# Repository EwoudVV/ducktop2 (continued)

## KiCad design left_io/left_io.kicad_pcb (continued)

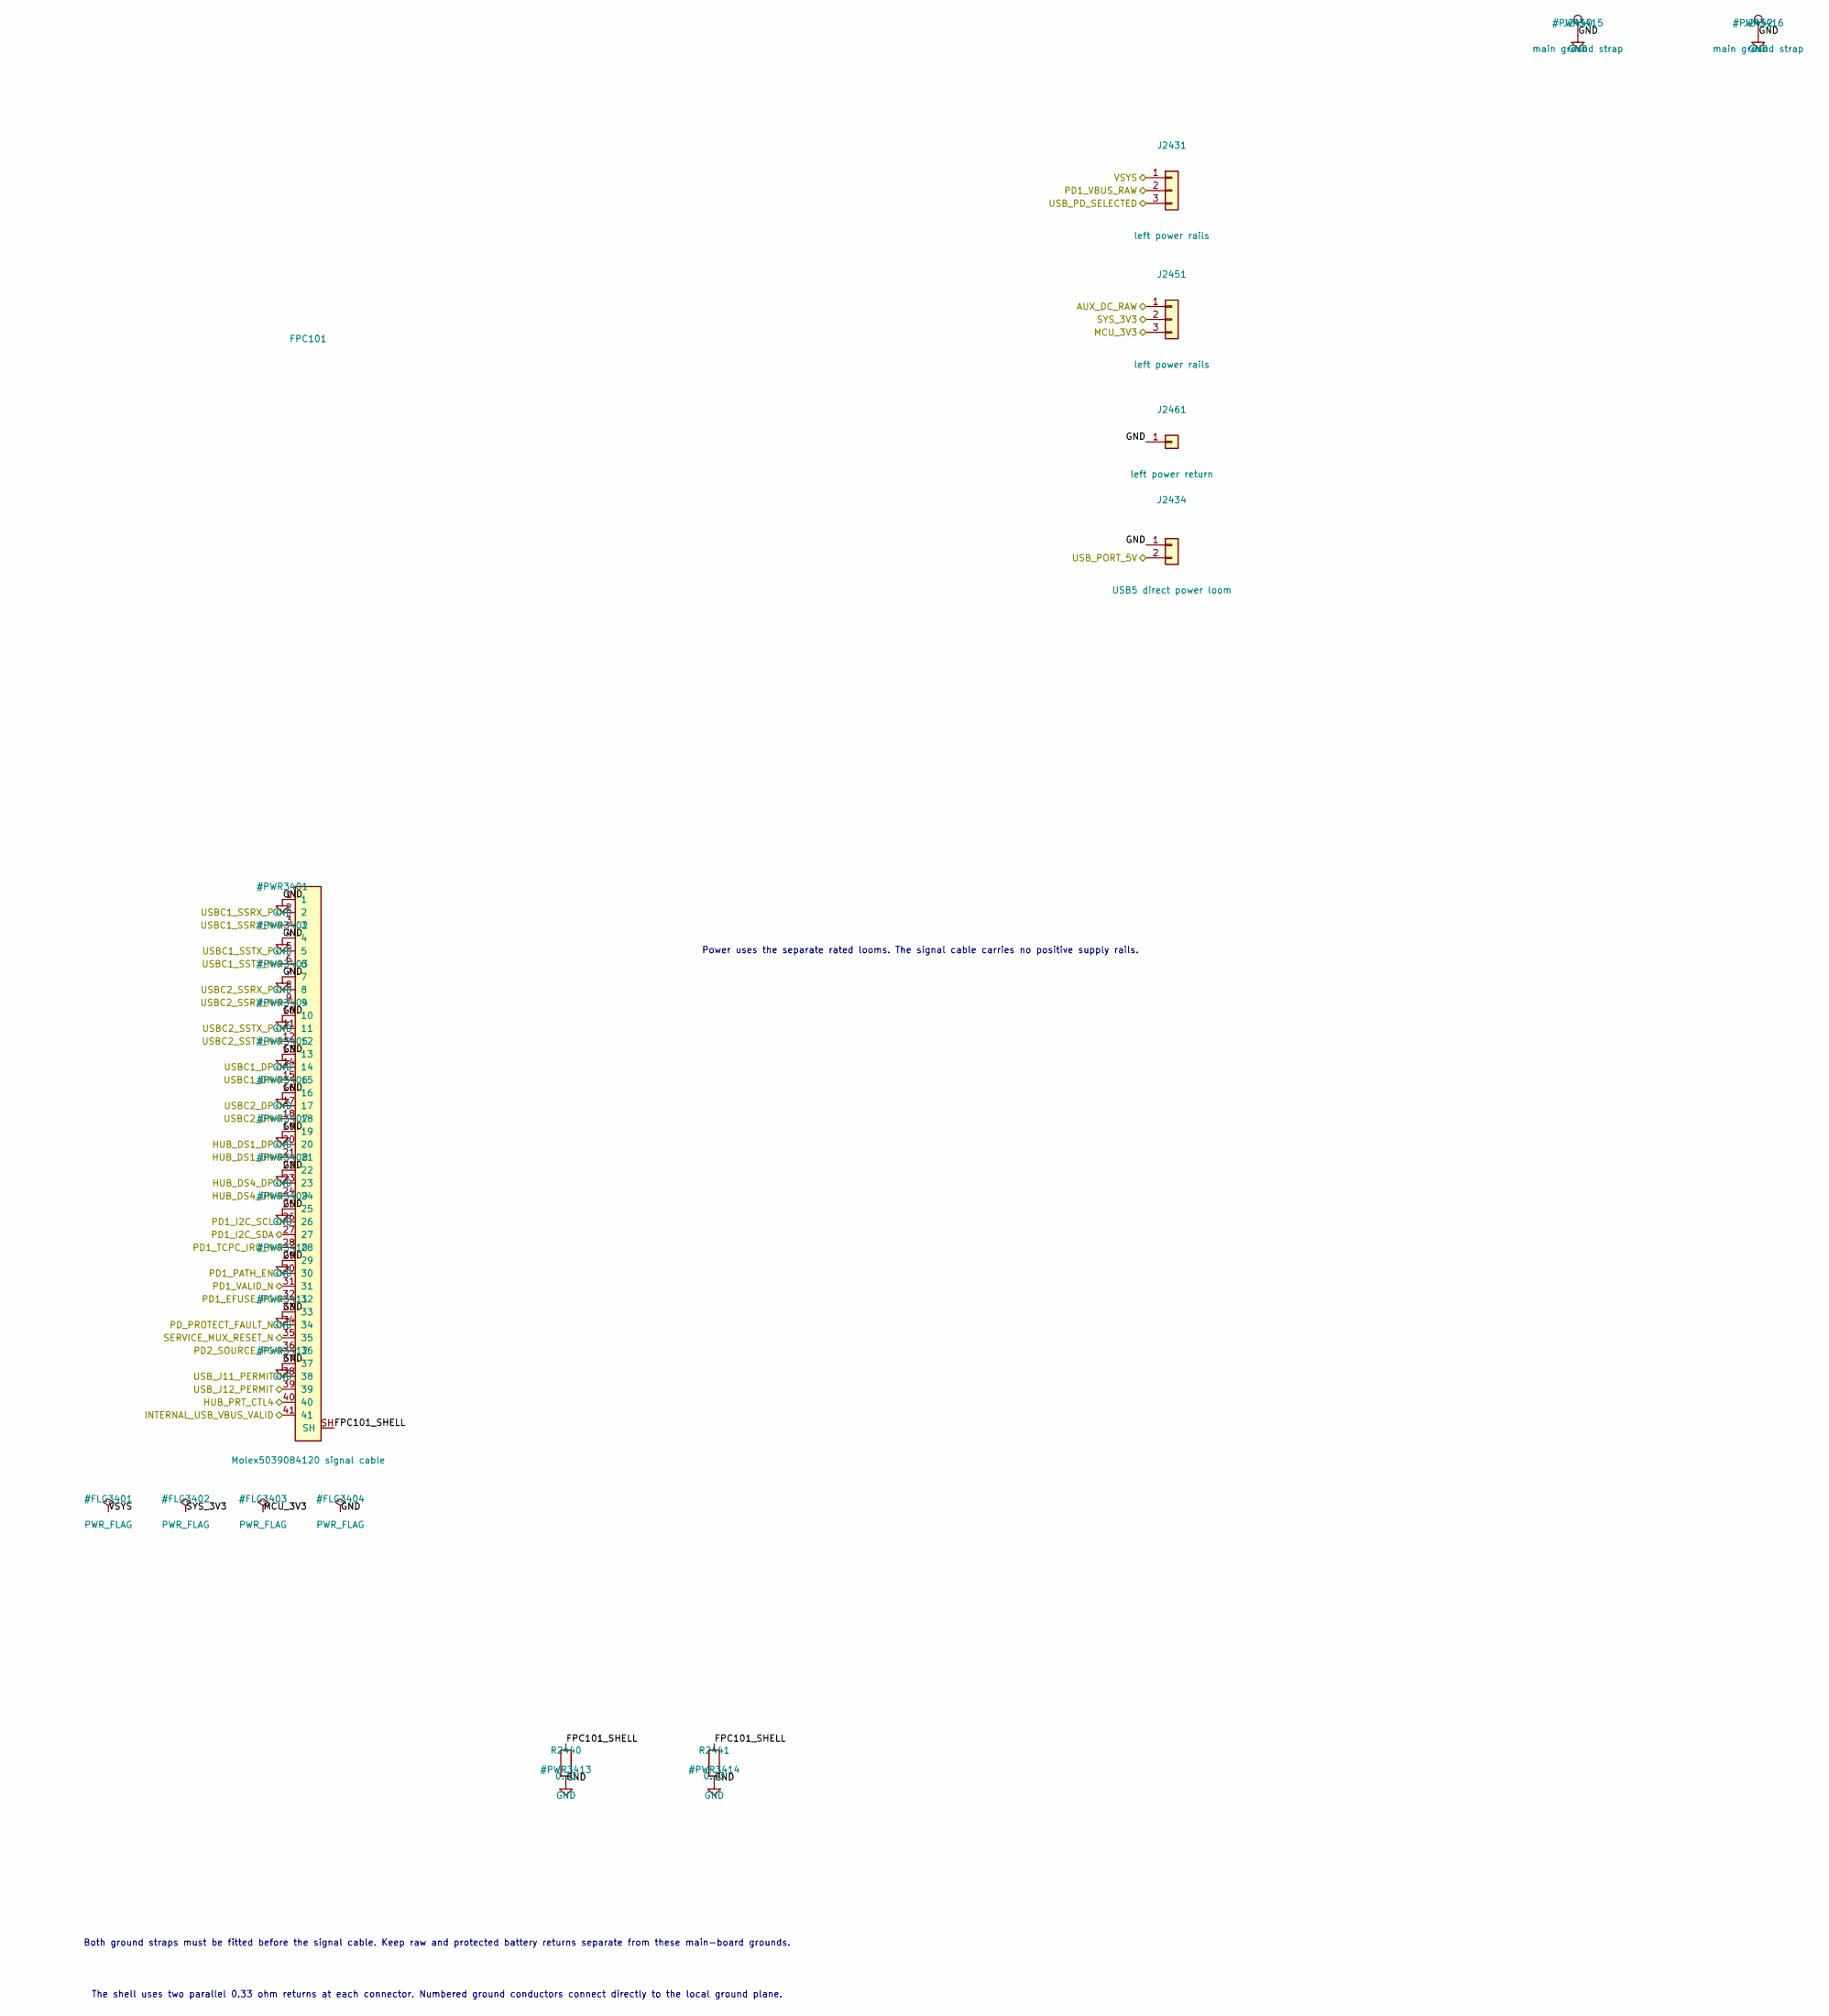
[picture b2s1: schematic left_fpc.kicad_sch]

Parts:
FPC101: Molex5039084120 signal cable; Molex_5039084120_1x41_P0.50mm_Horizontal; MPN 5039084120
J2431, J2451: left power rails; WAGO_2060_453_SMD; MPN 2060-453/998-404
J2434: USB5 direct power loom; AMASS_XT30PW-F30_G_Y; MPN XT30PW-F30.G.Y
J2440, J2442: main ground strap; SolderWirePad_1x01_SMD_5x10mm
J2461: left power return; WAGO_2060_451_SMD; MPN 2060-451/998-404
R2440, R2441: 0.33; R_0603_1608Metric; MPN ERJ3RQFR33V

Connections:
/AUX_DC_RAW: J2451.1; also elsewhere on the board
/FPC-1 (to Center)/FPC101_SHELL: FPC101.SH, R2440.1, R2441.1
/HUB_DS1_DN: FPC101.21; also elsewhere on the board
/HUB_DS1_DP: FPC101.20; also elsewhere on the board
/HUB_DS4_DN: FPC101.24; also elsewhere on the board
/HUB_DS4_DP: FPC101.23; also elsewhere on the board
/HUB_PRT_CTL4: FPC101.40; also elsewhere on the board
/INTERNAL_USB_VBUS_VALID: FPC101.41; also elsewhere on the board
/MCU_3V3: J2451.3; also elsewhere on the board
/PD1_EFUSE_PG: FPC101.32; also elsewhere on the board
/PD1_I2C_SCL: FPC101.26; also elsewhere on the board
/PD1_I2C_SDA: FPC101.27; also elsewhere on the board
/PD1_PATH_EN: FPC101.30; also elsewhere on the board
/PD1_TCPC_IRQ_N: FPC101.28; also elsewhere on the board
/PD1_VALID_N: FPC101.31; also elsewhere on the board
/PD1_VBUS_RAW: J2431.2; also elsewhere on the board
/PD2_SOURCE_PG: FPC101.36; also elsewhere on the board
/PD_PROTECT_FAULT_N: FPC101.34; also elsewhere on the board
/SERVICE_MUX_RESET_N: FPC101.35; also elsewhere on the board
/SYS_3V3: J2451.2; also elsewhere on the board
/USBC1_DN: FPC101.15; also elsewhere on the board
/USBC1_DP: FPC101.14; also elsewhere on the board
/USBC1_SSRX_N: FPC101.3; also elsewhere on the board
/USBC1_SSRX_P: FPC101.2; also elsewhere on the board
/USBC1_SSTX_N: FPC101.6; also elsewhere on the board
/USBC1_SSTX_P: FPC101.5; also elsewhere on the board
/USBC2_DN: FPC101.18; also elsewhere on the board
/USBC2_DP: FPC101.17; also elsewhere on the board
/USBC2_SSRX_N: FPC101.9; also elsewhere on the board
/USBC2_SSRX_P: FPC101.8; also elsewhere on the board
/USBC2_SSTX_N: FPC101.12; also elsewhere on the board
/USBC2_SSTX_P: FPC101.11; also elsewhere on the board
/USB_J11_PERMIT: FPC101.38; also elsewhere on the board
/USB_J12_PERMIT: FPC101.39; also elsewhere on the board
/USB_PD_SELECTED: J2431.3; also elsewhere on the board
/USB_PORT_5V: J2434.2; also elsewhere on the board
/VSYS: J2431.1; also elsewhere on the board
GND: FPC101.1, FPC101.4, FPC101.7, FPC101.10, FPC101.13, FPC101.16, FPC101.19, FPC101.22, FPC101.25, FPC101.29, FPC101.33, FPC101.37, J2434.1, J2440.1, J2442.1, J2461.1, R2440.2, R2441.2; also elsewhere on the board

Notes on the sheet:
Power uses the separate rated looms. The signal cable carries no positive supply rails.
Both ground straps must be fitted before the signal cable. Keep raw and protected battery returns separate from these main-board grounds.
The shell uses two parallel 0.33 ohm returns at each connector. Numbered ground conductors connect directly to the local ground plane.

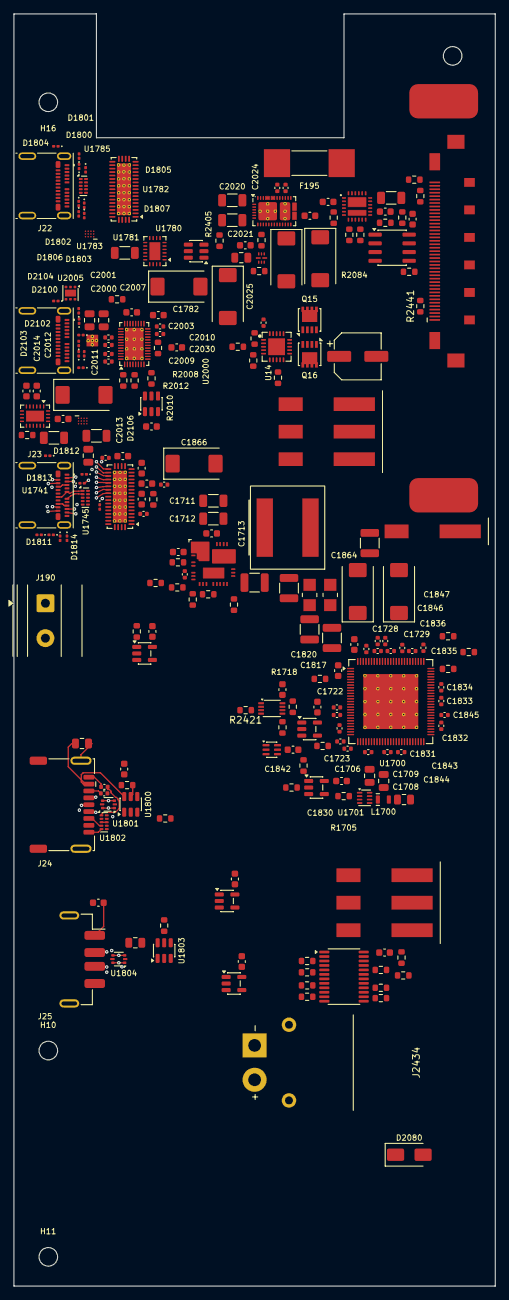
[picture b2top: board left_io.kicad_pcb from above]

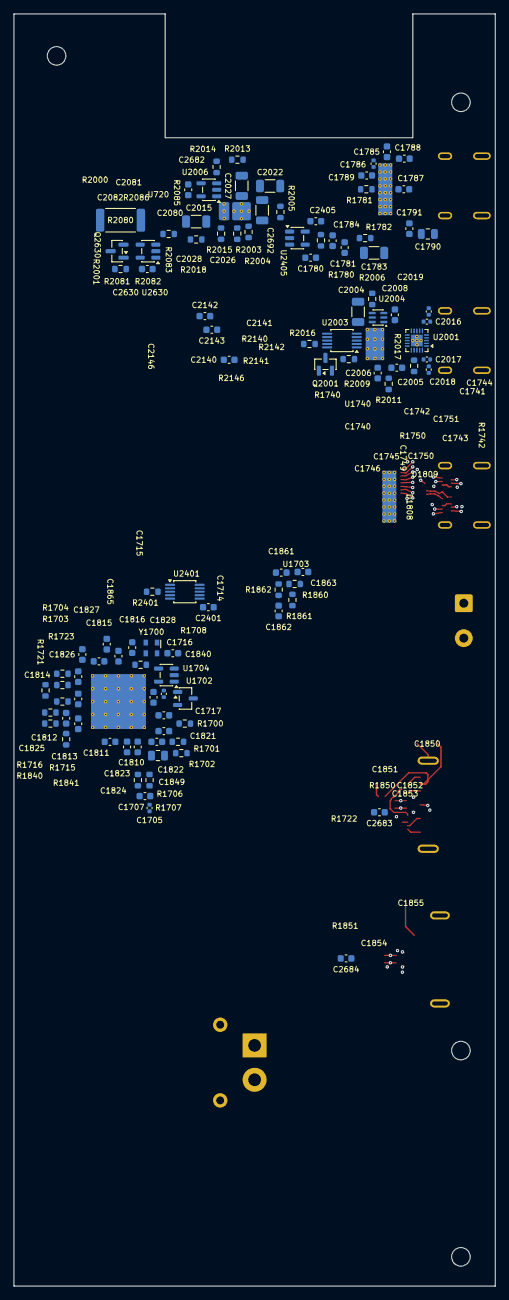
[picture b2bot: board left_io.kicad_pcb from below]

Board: 8 copper layers, 70.0 x 185.0 mm, 334 parts (103 on the bottom side), 220 nets.

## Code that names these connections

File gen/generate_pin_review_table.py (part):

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

def add_lm706a0(ref: str, prefix: str, sense: str, output: str, power_good: str) -> None:
    add_many(ref, (1, 2, 3, 27, 28, 29), "/VSYS", "All six converter input pins use VSYS.", LM706_SOURCE)
    add_many(ref, (6, 8, 17, 23, 24, 25, 26, 30), "GND",
             "Internal bias, forced PWM, analog ground and power/thermal returns.", LM706_SOURCE)
    for pin, suffix in {4: "BOOT", 5: "SW_BOOT", 9: "EN", 13: "CONFIG", 14: "RT",
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    clear_ref_contracts("U2", "U5", "U750", "U718", "U2660")
    add("U64", 3, "/Internal Services/TRACKPAD_EN", "Trackpad supply follows its hardware-qualified enable.", "gen/verify_design_contracts.py")
    aliases = {"/EC & MCU/NRST_NET":"/NRST_NET", "/PMIC_QON_ASSERT":"/MU_PROCHOT_RELEASE",
               "/PD1_EFUSE_FAULT_N":"/PD1_EFUSE_PG", "/PD2_EFUSE_FAULT_N":"/PD2_EFUSE_PG"}
    for key, contract in list(contracts.items()):
        if contract.expected in aliases:
            contracts[key] = Contract(aliases[contract.expected], "Reset and source-control signal for the 100 W power revision.",
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
    # Battery power entry and aux/random DC input.
    for pin in (1, 2):
        add("J2", pin, "/Power & Battery/PACK_POS_RAW", "Paired raw pack-positive power contact.", "Ducktop2 autonomous 3S protection contract")
    for pin in (3, 4):
        add("J2", pin, "/Power & Battery/PACK_NEG_RAW", "Paired raw pack-negative power contact before protector shunt/FETs.", "Ducktop2 autonomous 3S protection contract")
    add("J2", 5, "/Power & Battery/CELL1_TAP", "Cell-1 positive / cell-2 negative balance tap.", "TI BQ77915 3S connection contract")
    add("J2", 6, "/Power & Battery/CELL2_TAP", "Cell-2 positive / cell-3 negative balance tap.", "TI BQ77915 3S connection contract")
    add("F1", 1, "/Power & Battery/PACK_POS_RAW", "Main pack fuse input is raw pack positive.", "Ducktop2 battery safety review")
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    ):
        add(ref, pin, net, note, "Analog Devices LTC4368-1 latch/retry contract")
    for ref, drain in [("Q11", "/Power & Battery/BAT_PROT_VIN"), ("Q12", "/Power & Battery/BAT_PROT_SENSE")]:
        add_many(ref, [1, 2, 3], "/Power & Battery/BAT_PROT_FET_COMMON", "Back-to-back MOSFET source pins share the protected common-source node.", "Analog Devices LTC4368-1 reverse-protection topology")
        add(ref, 4, "/Power & Battery/BAT_PROT_GATE", "MOSFET gate is driven through the protected gate network.", "Analog Devices LTC4368-1 reverse-protection topology")
        add(ref, 5, drain, "MOSFET drain terminates its side of the protected pack path.", "Analog Devices LTC4368-1 reverse-protection topology")
    add("RS10", 1, "/Power & Battery/BAT_PROT_SENSE", "High-side shunt controller-side sense node.", "Ducktop2 protected-pack contract")
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                16:"SEL_STAGE2", 17:"/USB_PD_SELECTED", 18:"MAIN_SEL_INTVCC",
                19:"MAIN_SEL_INTVCC", 20:"GND", 21:"GND"},
        "U16": {1:"ST2_SEL_TMR", 2:"ST2_USB_UV", 3:"ST2_USB_OV",
                 4:"ST2_AUX_UV", 5:"ST2_AUX_OV", 6:"/PD2_VALID_N", 8:"GND",
                 10:"ST2_SEL_INTVCC", 11:"ST2_AUX_GATE", 12:"ST2_AUX_FET_COMMON",
                 13:"ST2_USB_GATE", 14:"ST2_USB_FET_COMMON", 15:"SEL_STAGE2",
                 16:"AUX_DC_PROTECTED", 17:"/PD2_VBUS_GATED", 18:"ST2_SEL_INTVCC",
                 19:"ST2_SEL_INTVCC", 20:"GND", 21:"GND"},
    }
    def selector_net(name):
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        ("Q22", "USB_MAIN_GATE", "USB_MAIN_FET_COMMON", "VBUS_COMBINED"),
        ("Q23", "ST2_AUX_GATE", "ST2_AUX_FET_COMMON", "AUX_DC_PROTECTED"),
        ("Q24", "ST2_AUX_GATE", "ST2_AUX_FET_COMMON", "SEL_STAGE2"),
        ("Q26", "ST2_USB_GATE", "ST2_USB_FET_COMMON", "/PD2_VBUS_GATED"),
        ("Q27", "ST2_USB_GATE", "ST2_USB_FET_COMMON", "SEL_STAGE2"),
        ("Q28", "ST2_MAIN_GATE", "ST2_MAIN_FET_COMMON", "SEL_STAGE2"),
        ("Q29", "ST2_MAIN_GATE", "ST2_MAIN_FET_COMMON", "VBUS_COMBINED"),
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        ("R730", "/USB_PD_SELECTED", "USB_MAIN_UV"), ("R731", "USB_MAIN_UV", "USB_MAIN_OV"),
        ("R732", "USB_MAIN_OV", "GND"), ("R733", "AUX_DC_PROTECTED", "ST2_AUX_UV"),
        ("R734", "ST2_AUX_UV", "ST2_AUX_OV"), ("R735", "ST2_AUX_OV", "GND"),
        ("R741", "/PD2_VBUS_GATED", "ST2_USB_UV"), ("R742", "ST2_USB_UV", "ST2_USB_OV"),
        ("R743", "ST2_USB_OV", "GND"), ("R744", "SEL_STAGE2", "ST2_MAIN_UV"),
        ("R745", "ST2_MAIN_UV", "ST2_MAIN_OV"), ("R746", "ST2_MAIN_OV", "GND"),
    ):
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        ("C747", "ST2_MAIN_FET_COMMON"), ("C748", "SEL_STAGE2"),
        ("C749", "ST2_SEL_INTVCC"), ("C715", "ST2_SEL_TMR"),
        ("C746", "VBUS_COMBINED"), ("C2685", "SEL_STAGE2"),
        ("C2686", "/PD2_VBUS_GATED"), ("C2687", "ST2_USB_FET_COMMON"),
        ("C2688", "VBUS_COMBINED"),
    ):
        add(ref, 1, selector_net(net), "Selector bypass, hold-up, or timer capacitor.", selector)
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    for ref, source in (
        ("D710", "/Power & Battery/BAT_CHARGER"),
        ("D711", "/Power & Battery/AUX_DC_PROTECTED"),
        ("D712", "/PD1_VBUS_RAW"),
        ("D713", "/PD2_VBUS_RAW"),
        ("D714", "/PD3_VBUS_RAW"),
    ):
        add(ref, 1, "/Power & Battery/AON_OR_RAW", "Schottky cathode joins the aggregate always-on eFuse input.", aon_or)
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        9: "/Power & Battery/VBUS_COMBINED",
        10: "GND",
        11: "GND",
        12: "/Power & Battery/PMIC_QON_PIN",
        13: "/Power & Battery/CHG_CE_HW_N",
        14: "/I2C_SCL",
        15: "/I2C_SDA",
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    add("R705", 1, "/Power & Battery/CHG_TS_FIXED", "Fixed TS divider bottom holds a valid room-temperature ratio.", bq)
    add("R705", 2, "GND", "Fixed TS divider returns to ground.", bq)
    for pin in (1, 2, 3):
        add("Q25", pin, "/Power & Battery/BAT_CHARGER", "BQ25798 ship-FET source is on the charger-side BAT node.", bq)
    add("Q25", 4, "/Power & Battery/SDRV_GATE", "BQ25798 SDRV directly controls the qualified ship FET gate.", bq)
    add("Q25", 5, "/PACK_POS_FUSED", "Ship-FET drain connects to the protected pack for electronic ship/hard-off.", bq)
    for ref, pin, net, note in (
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        ("R13", 2, "GND", "QON gate pull-down return."),
        ("Q702", 1, "/PMIC_QON_ASSERT", "Active-high EC pulse drives the QON open-drain gate."),
        ("Q702", 2, "GND", "QON open-drain source."),
        ("Q702", 3, "/Power & Battery/PMIC_QON_PIN", "QON open-drain drain; no dead-rail pull-up is allowed."),
        ("D715", 1, "/CASE_PWRBTN_N", "Case-button cathode shared only by the two isolation diodes."),
        ("D715", 2, "/Power & Battery/PMIC_QON_PIN", "Case button can wake the BQ25798 through a Schottky anode."),
        ("D716", 1, "/CASE_PWRBTN_N", "Case-button cathode shared only by the two isolation diodes."),
        ("D716", 2, "/MU_PWRBTN_N", "Case button reaches Mu PWRBTN through an independent Schottky anode."),
    ):
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
    # EC buck and core STM32 pins that are easy to get catastrophically wrong.
    stm = "ST STM32F407 datasheet plus Ducktop2 EC core contract"
    add_many("U4", [6, 11, 19, 21, 22, 28, 50, 75, 100], "/MCU_3V3", "STM32 VDD/VBAT/VDDA pins require 3.3 V rail.", stm)
    add_many("U4", [10, 20, 27, 74, 99], "GND", "STM32 VSS/VSSA pins require ground.", stm)
    for pin, net in {49: "/EC & MCU/VCAP1_NODE", 73: "/EC & MCU/VCAP2_NODE", 94: "/EC & MCU/BOOT0_NET", 14: "/EC & MCU/NRST_NET", 72: "/EC & MCU/SWDIO_NET", 76: "/EC & MCU/SWCLK_NET"}.items():
        add("U4", pin, net, "STM32 reset, boot, SWD, and VCAP pins follow the EC core contract.", stm)
    for pin, net in {8: "/EC & MCU/LSE_IN", 9: "/EC & MCU/LSE_OUT",
                     12: "/EC & MCU/HSE_IN", 13: "/EC & MCU/HSE_OUT"}.items():
        add("U4", pin, net, "STM32 oscillator pin follows the qualified prototype oscillator contract.", stm)
    for pin, net, requirement in [
        (47, "/RADIO_VHF_UART_TX", "PB10 is USART3_TX for VHF radio hardware UART."),
        (48, "/RADIO_VHF_UART_RX", "PB11 is USART3_RX for VHF radio hardware UART."),
        (63, "/RADIO_UHF_UART_TX", "PC6 is USART6_TX for UHF radio hardware UART."),
        (64, "/RADIO_UHF_UART_RX", "PC7 is USART6_RX for UHF radio hardware UART."),
        (67, "/WIFI_W_DISABLE1_N_EC", "PA8 drives the powered-off-isolated WLAN disable input."),
        (68, "/GNSS_UART_TX", "PA9 is USART1_TX for GNSS hardware UART."),
        (69, "/GNSS_UART_RX", "PA10 is USART1_RX for GNSS hardware UART."),
        (77, "/WIFI_W_DISABLE2_N_EC", "PA15 drives the powered-off-isolated Bluetooth disable input."),
        (36, "/TRACKPAD_FAULT_N", "PB1 reads the trackpad current-limited branch fault output."),
        (44, "/MU_12V_ENABLE", "PE13 explicitly enables the regulated Mu 12 V rail after source qualification."),
        (45, "/MU_S0_HIGH", "PE14 reads the Mu PSON/S0 status signal."),
        (46, "/MU_12V_PG", "PE15 reads the regulated Mu 12 V power-good signal."),
        (42, "/AUDIO_MIC_EN", "PE11 controls the fail-off microphone rail; the privacy indicator monitors the actual MIC_2V8 output."),
        (15, "/KB_RGB_PWR_EN", "PC0 enables both the current-limited keyboard RGB rail and its level buffer."),
        (16, "/KB_RGB_FAULT_N", "PC1 reads the active-low keyboard RGB power-switch fault output."),
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
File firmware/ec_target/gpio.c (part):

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    GPIOC->ODR = (1u << 8) | (1u << 9) | (1u << 10);
    GPIOD->ODR = 0u;
    GPIOE->ODR = 0u;
    /* Preserve SWD on PA13/PA14 through normal startup. */
    GPIOA->MODER = (2u << 26) | (2u << 28);
    GPIOA->PUPDR = (1u << 26) | (2u << 28);
    GPIOA->AFR[1] &= ~((0xFu << 20) | (0xFu << 24));
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
    /* ---- Port A ---- */

    /* PA0: MU_PWRBTN_N - Output, open-drain, high (inactive) */
    GPIOA->MODER   |= GPIO_MODER_OUTPUT << (0 * 2);
    GPIOA->OTYPER  |= GPIO_OTYPER_OD << 0;
    GPIOA->PUPDR   |= GPIO_PUPDR_PU << (0 * 2);
    GPIOA->ODR     |= 1u << 0;

    /* PA1: BQ_ALERT - Input, pull-up */
    GPIOA->PUPDR   |= GPIO_PUPDR_PU << (1 * 2);

    /* PA2: CHG_INT_N - Input, pull-up */
    GPIOA->PUPDR   |= GPIO_PUPDR_PU << (2 * 2);

    /* PA3: MU_PROCHOT_RELEASE - low keeps the module throttled. */
    GPIOA->MODER   |= GPIO_MODER_OUTPUT << (3 * 2);

    /* PA4: CHG_ENABLE - Output, push-pull, low (charger off) */
    GPIOA->MODER   |= GPIO_MODER_OUTPUT << (4 * 2);

    /* PA5: MU_RSTBTN_N - Output, open-drain, high (inactive) */
    GPIOA->MODER   |= GPIO_MODER_OUTPUT << (5 * 2);
    GPIOA->OTYPER  |= GPIO_OTYPER_OD << 5;
    GPIOA->ODR     |= 1u << 5;

    /* PA6: AUX_DC_ADC - Analog */
    GPIOA->MODER   |= GPIO_MODER_ANALOG << (6 * 2);

    /* PA7: THERM_SKIN_ADC - Analog */
    GPIOA->MODER   |= GPIO_MODER_ANALOG << (7 * 2);

    /* PA8: WIFI_W_DISABLE1_N_EC - Output, push-pull, high (disabled) */
    GPIOA->MODER   |= GPIO_MODER_OUTPUT << (8 * 2);
    GPIOA->ODR     |= 1u << 8;

    /* PA9: GNSS_UART_TX - AF7 (USART1) */
    GPIOA->MODER   |= GPIO_MODER_AF << (9 * 2);
    GPIOA->AFR[1]     = (GPIOA->AFR[1] & ~(0xFu << 4)) | (GPIO_AF7 << 4);

    /* PA10: GNSS_UART_RX - AF7 (USART1) */
    GPIOA->MODER   |= GPIO_MODER_AF << (10 * 2);
    GPIOA->AFR[1]     = (GPIOA->AFR[1] & ~(0xFu << 8)) | (GPIO_AF7 << 8);

    /* PA11: MCU_USB_DN - AF10 (OTG_FS) */
    GPIOA->MODER   |= GPIO_MODER_AF << (11 * 2);
    GPIOA->AFR[1]     = (GPIOA->AFR[1] & ~(0xFu << 12)) | (GPIO_AF10 << 12);

    /* PA12: MCU_USB_DP - AF10 (OTG_FS) */
    GPIOA->MODER   |= GPIO_MODER_AF << (12 * 2);
    GPIOA->AFR[1]     = (GPIOA->AFR[1] & ~(0xFu << 16)) | (GPIO_AF10 << 16);

    /* PA13: SWDIO - leave as default (AF0, pull-up) */

    /* PA14: SWCLK - leave as default (AF0, pull-down) */

    /* PA15: WIFI_W_DISABLE2_N_EC - Output, push-pull, high (disabled) */
    GPIOA->MODER   |= GPIO_MODER_OUTPUT << (15 * 2);
    GPIOA->ODR     |= 1u << 15;

    /* ---- Port B ---- */

    /* PB0: THERM_MU_ADC - Analog */
    GPIOB->MODER   |= GPIO_MODER_ANALOG << (0 * 2);

    /* PB1: TRACKPAD_FAULT_N - Input, pull-up */
    GPIOB->PUPDR   |= GPIO_PUPDR_PU << (1 * 2);

    /* PB2: PD2_VALID_N - Input, pull-up */
    GPIOB->PUPDR   |= GPIO_PUPDR_PU << (2 * 2);

    /* PB3: (JTDO/SWO) - leave as default */

    /* PB4: PD2_TCPC_IRQ_N - Input, pull-up */
    GPIOB->PUPDR   |= GPIO_PUPDR_PU << (4 * 2);

    /* PB5: RADIO_DB_PWR_EN - Output, push-pull, low (off) */
    GPIOB->MODER   |= GPIO_MODER_OUTPUT << (5 * 2);

    /* PB6: I2C1_SCL - AF4 */
    GPIOB->MODER   |= GPIO_MODER_AF << (6 * 2);
    GPIOB->OTYPER  |= GPIO_OTYPER_OD << 6;
    GPIOB->PUPDR   |= GPIO_PUPDR_PU << (6 * 2);
    GPIOB->OSPEEDR |= GPIO_OSPEEDR_HIGH << (6 * 2);
    GPIOB->AFR[0]     = (GPIOB->AFR[0] & ~(0xFu << 24)) | (GPIO_AF4 << 24);

    /* PB7: I2C1_SDA - AF4 */
    GPIOB->MODER   |= GPIO_MODER_AF << (7 * 2);
    GPIOB->OTYPER  |= GPIO_OTYPER_OD << 7;
    GPIOB->PUPDR   |= GPIO_PUPDR_PU << (7 * 2);
    GPIOB->OSPEEDR |= GPIO_OSPEEDR_HIGH << (7 * 2);
    GPIOB->AFR[0]     = (GPIOB->AFR[0] & ~(0xFu << 28)) | (GPIO_AF4 << 28);

    /* PB8: GNSS_EXTINT - Input, pull-down */
    GPIOB->PUPDR   |= GPIO_PUPDR_PD << (8 * 2);

    /* PB9: PD_PROTECT_FAULT_N - Input, pull-up */
    GPIOB->PUPDR   |= GPIO_PUPDR_PU << (9 * 2);

    /* PB10: RADIO_VHF_UART_TX - AF7 (USART3) */
    GPIOB->MODER   |= GPIO_MODER_AF << (10 * 2);
    GPIOB->AFR[1]     = (GPIOB->AFR[1] & ~(0xFu << 8)) | (GPIO_AF7 << 8);

    /* PB11: RADIO_VHF_UART_RX - AF7 (USART3) */
    GPIOB->MODER   |= GPIO_MODER_AF << (11 * 2);
    GPIOB->AFR[1]     = (GPIOB->AFR[1] & ~(0xFu << 12)) | (GPIO_AF7 << 12);

    /* PB12: SERVICE_MUX_RESET_REQ_N - Output, push-pull, low (reset held) */
    GPIOB->MODER   |= GPIO_MODER_OUTPUT << (12 * 2);

    /* PB13: GNSS_RESET_N - Output, push-pull, low (reset asserted) */
    GPIOB->MODER   |= GPIO_MODER_OUTPUT << (13 * 2);

    /* PB14: GNSS_PPS - Input, pull-down */
    GPIOB->PUPDR   |= GPIO_PUPDR_PD << (14 * 2);

    /* PB15: RADIO_VHF_PTT_N - Output, push-pull, high (inactive) */
    GPIOB->MODER   |= GPIO_MODER_OUTPUT << (15 * 2);
    GPIOB->ODR     |= 1u << 15;

    /* ---- Port C ---- */

    /* PC0: KB_RGB_PWR_EN - Output, push-pull, low (off) */
    GPIOC->MODER   |= GPIO_MODER_OUTPUT << (0 * 2);

    /* PC1: KB_RGB_FAULT_N - Input, pull-up */
    GPIOC->PUPDR   |= GPIO_PUPDR_PU << (1 * 2);

    /* PC2: RADIO_VHF_RF_SEL_3V3 - Output, push-pull, low */
    GPIOC->MODER   |= GPIO_MODER_OUTPUT << (2 * 2);

    /* PC3: RADIO_UHF_RF_SEL_3V3 - Output, push-pull, low */
    GPIOC->MODER   |= GPIO_MODER_OUTPUT << (3 * 2);

    /* PC4: PD1_VALID_N - Input, pull-up */
    GPIOC->PUPDR   |= GPIO_PUPDR_PU << (4 * 2);

    /* PC5: FAN_TACH - Input, no internal pull (R206 8.2k to MCU_3V3 idles
     * the open-collector FG line high; C209 3.9n filters it) */
    GPIOC->MODER   |= GPIO_MODER_INPUT << (5 * 2);

    /* PC6: RADIO_UHF_UART_TX - AF8 (USART6) */
    GPIOC->MODER   |= GPIO_MODER_AF << (6 * 2);
    GPIOC->AFR[0]     = (GPIOC->AFR[0] & ~(0xFu << 24)) | (GPIO_AF8 << 24);

    /* PC7: RADIO_UHF_UART_RX - AF8 (USART6) */
    GPIOC->MODER   |= GPIO_MODER_AF << (7 * 2);
    GPIOC->AFR[0]     = (GPIOC->AFR[0] & ~(0xFu << 28)) | (GPIO_AF8 << 28);

    /* PC8: RADIO_UHF_PTT_N - Output, push-pull, high (inactive) */
    GPIOC->MODER   |= GPIO_MODER_OUTPUT << (8 * 2);
    GPIOC->ODR     |= 1u << 8;

    /* PC9: RADIO_VHF_PD_N - Output, push-pull, high (inactive) */
    GPIOC->MODER   |= GPIO_MODER_OUTPUT << (9 * 2);
    GPIOC->ODR     |= 1u << 9;

    /* PC10: RADIO_UHF_PD_N - Output, push-pull, high (inactive) */
    GPIOC->MODER   |= GPIO_MODER_OUTPUT << (10 * 2);
    GPIOC->ODR     |= 1u << 10;

    /* PC11: RADIO_VHF_SQL - Input, pull-down */
    GPIOC->PUPDR   |= GPIO_PUPDR_PD << (11 * 2);

    /* PC12: RADIO_UHF_SQL - Input, pull-down */
    GPIOC->PUPDR   |= GPIO_PUPDR_PD << (12 * 2);

    /* PC13: SOURCE_MGR_INT_N - Input, pull-up */
    GPIOC->PUPDR   |= GPIO_PUPDR_PU << (13 * 2);

    /* PC14: LSE_IN - leave as default for LSE */
    /* PC15: LSE_OUT - leave as default for LSE */

    /* ---- Port D - Keyboard Columns ---- */

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
    /* ---- Port E ---- */

    /* PE0-PE7: Keyboard rows - Output, push-pull, low */
    for (int i = 0; i <= 7; i++) {
        GPIOE->MODER |= GPIO_MODER_OUTPUT << (i * 2);
    }

    /* PE8: PD1_TCPC_IRQ_N - Input, pull-up */
    GPIOE->PUPDR   |= GPIO_PUPDR_PU << (8 * 2);

    /* PE9: FAN_PWM - AF1 (TIM1_CH1) */
    GPIOE->MODER   |= GPIO_MODER_AF << (9 * 2);
    GPIOE->AFR[1]     = (GPIOE->AFR[1] & ~(0xFu << 4)) | (GPIO_AF1 << 4);

    /* PE10: LID_CLOSED_N - Input, pull-up */
    GPIOE->PUPDR   |= GPIO_PUPDR_PU << (10 * 2);

    /* PE11: AUDIO_MIC_EN - Output, push-pull, low (off) */
    GPIOE->MODER   |= GPIO_MODER_OUTPUT << (11 * 2);

    /* PE12: AUDIO_AMP_EC_EN - Output, push-pull, low (off) */
    GPIOE->MODER   |= GPIO_MODER_OUTPUT << (12 * 2);

    /* PE13: MU_12V_ENABLE - Output, push-pull, low (off) */
    GPIOE->MODER   |= GPIO_MODER_OUTPUT << (13 * 2);

    /* PE14: MU_S0_HIGH - R768 supplies the module's required pull-up. */
    GPIOE->PUPDR   &= ~(3u << (14 * 2));

    /* PE15: MU_12V_PG - R762/R2671 set both levels, including rail-off.
     * An internal pull-down loads the divider and can hide a valid rail. */
    GPIOE->PUPDR   &= ~(3u << (15 * 2));
}
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void gpio_set_pd_path_enable_a(bool enable)
{
    (void)enable;
    /* PD1_PATH_EN is driven through TCA9539 (source manager), not a direct GPIO.
     * Actual control via i2c.c tca9539_write_register(). */
}

void gpio_set_pd_path_enable_b(bool enable)
{
    (void)enable;
    /* PD2_PATH_EN is driven through TCA9539. */
}

bool gpio_get_pd1_valid_n(void)
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    }
}

/* ---- ADC1: AUX_DC (PA6), skin NTC (PA7), Mu NTC (PB0) ---- */

/*
 * ADC1 input channels for the monitored signals, per RM0090 Table 8
 * (PA6=IN6, PA7=IN7, PB0=IN8) and verified against the schematic
 * (gen/generate_pin_review_table.py lines 524-527; the EC MCU sheet maps
 * pins 31/32/35 to AUX_DC_ADC/THERM_SKIN_ADC/THERM_MU_ADC on those ports).
 * Note: PA3 (ADC1_IN3) is MU_PROCHOT_RELEASE, so the previous hardcoded
 * channel 3 for AUX_DC sampled the wrong signal.
 */
#define ADC_CHANNEL_AUX_DC       6u
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    return adc_read_channel(ADC_CHANNEL_THERM_MU);
}

/* ---- TIM1_CH1 fan PWM (PE9, AF1) ---- */

/*
 * Signal chain (schematic, gen/generate_internal_services_sheet.py): FAN_PWM
 * (PE9) -> R207 100R -> Q200 (2N7002KT1G) gate; Q200 drains J52 pin 4
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
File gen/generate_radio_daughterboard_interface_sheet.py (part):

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    )
    s.place("R2300", "R", "100k radio eFuse enable pulldown", 20, 76.2,
            footprint=FOOTPRINTS["R"],
            pin_nets={"1": ("RADIO_DB_PWR_EN", "hier"), "2": ("GND", "local")})
    s.place("R2301", "R", "1.65k 0.1% radio eFuse ILM about 2.0A", 20, 88.9,
            footprint=FOOTPRINTS["R"],
            pin_nets={"1": ("RADIO_DB_ILM", "local"), "2": ("GND", "local")})
    s.place("C2300", "C", "4.7n radio eFuse controlled rise", 20, 101.6,
            footprint=FOOTPRINTS["C_1n"],
            pin_nets={"1": ("RADIO_DB_DVDT", "local"), "2": ("GND", "local")})
    for ref, value, net, y, fp in (
        ("C2301", "10u SYS_5V radio eFuse input", "SYS_5V", 114.3, "C_10u"),
        ("C2302", "100n SYS_5V radio eFuse input HF", "SYS_5V", 127.0, "C_100n"),
        ("C2304", "100n RADIO_DB_5V output HF", "RADIO_DB_5V", 152.4, "C_100n"),
    ):
        s.place(ref, "C", value, 20, y, footprint=FOOTPRINTS[fp],
                pin_nets={"1": (net, "hier" if net == "SYS_5V" else "local"), "2": ("GND", "local")})
    s.place("C2303", "C", "22u 25V RADIO_DB_5V bulk; TI characterized part", 20, 139.7,
            footprint=FOOTPRINTS["C_1210"],
            pin_nets={"1": ("RADIO_DB_5V", "local"), "2": ("GND", "local")},
            extra_props={"Manufacturer": "Murata", "MPN": "GRM32ER71E226KE15L"})

    # TLV803 asserts low until the switched rail is above 4.3 V. Its open-drain
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    s.place(
        "U2301", "TLV803EA43RDBZR", "TLV803EA43 4.3V radio rail supervisor", 260, 90,
        footprint=FOOTPRINTS["TLV803EA43RDBZR"],
        pin_nets={"1": ("RADIO_DB_PG_RAW", "local"), "2": ("GND", "local"), "3": ("RADIO_DB_5V", "local")},
        extra_props={"Manufacturer": "Texas Instruments", "MPN": "TLV803EA43RDBZR"},
    )
    s.place("R2302", "R", "2.2k supervisor pull-up to switched 5V", 225, 115,
            footprint=FOOTPRINTS["R"],
            pin_nets={"1": ("RADIO_DB_5V", "local"), "2": ("RADIO_DB_PG_RAW", "local")})
    s.place("R2303", "R", "10k radio PG level-divider top", 260, 115,
            footprint=FOOTPRINTS["R"],
            pin_nets={"1": ("RADIO_DB_PG_RAW", "local"), "2": ("RADIO_DB_PG_DIV", "local")})
    s.place("R2304", "R", "20k radio PG level-divider bottom", 300, 115,
            footprint=FOOTPRINTS["R"],
            pin_nets={"1": ("RADIO_DB_PG_DIV", "local"), "2": ("GND", "local")})
    s.place(
        "U2302", "74LVC1G17", "SN74LVC1G17DBVR radio PG level restore", 350, 100,
        footprint=FOOTPRINTS["SN74LVC1G17DBV"],
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    )
    s.place("C2305", "C", "100n radio PG buffer local", 350, 125,
            footprint=FOOTPRINTS["C_100n"],
            pin_nets={"1": ("MCU_3V3", "hier"), "2": ("GND", "local")})
    s.place("R2305", "R", "10k radio eFuse/shared fault pull-up", 420, 76.2,
            footprint=FOOTPRINTS["R"],
            pin_nets={"1": ("MCU_3V3", "hier"), "2": ("RADIO_DB_FAULT_N", "hier")})
    s.place("R2306", "R", "10k daughterboard-present pull-up; absent=high", 420, 88.9,
            footprint=FOOTPRINTS["R"],
            pin_nets={"1": ("MCU_3V3", "hier"), "2": ("RADIO_DB_PRESENT_N", "hier")})

    s.text(20, 190.5, "== USB codec isolation: no phantom device or back-power when daughterboard is absent ==")
    s.place(
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    )
    s.place("R2307", "R", "100k USB switch disable pull-up", 20, 228.6,
            footprint=FOOTPRINTS["R"],
            pin_nets={"1": ("MCU_3V3", "hier"), "2": ("RADIO_USB_OE_N", "local")})
    s.place("Q2300", "Q_NMOS_SOT23_GSD", "2N7002K radio-PG USB enable", 20, 241.3,
            footprint=FOOTPRINTS["Q_NMOS"],
            pin_nets={"1": ("RADIO_DB_PG", "hier"), "2": ("GND", "local"), "3": ("RADIO_USB_OE_N", "local")},
            extra_props={"Manufacturer": "onsemi", "MPN": "2N7002KT1G"})
    s.place("C2306", "C", "100n USB switch local", 20, 254,
            footprint=FOOTPRINTS["C_100n"],
            pin_nets={"1": ("MCU_3V3", "hier"), "2": ("GND", "local")})
    s.place(
        "U2304", "TPS2553D", "TPS2553D radio codec VBUS gate 0.20A", 330, 245,
        footprint=FOOTPRINTS["TPS2553DDBV"],
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    )
    s.place("R2308", "R", "133k 1% TPS2553 current limit about 0.20A", 430, 228.6,
            footprint=FOOTPRINTS["R"],
            pin_nets={"1": ("RADIO_CODEC_ILIM", "local"), "2": ("GND", "local")},
            extra_props={"Manufacturer": "Yageo", "MPN": "RC0603FR-07133KL"})
    s.place("C2307", "C", "1u radio codec VBUS gate input", 430, 241.3,
            footprint=FOOTPRINTS["C_1u"],
            pin_nets={"1": ("RADIO_CODEC_USB_VBUS_HOST", "hier"), "2": ("GND", "local")})
    s.place("C2308", "C", "10u radio codec VBUS gate output", 430, 254,
            footprint=FOOTPRINTS["C_10u"],
            pin_nets={"1": ("RADIO_CODEC_USB_VBUS_DB", "local"), "2": ("GND", "local")})
    s.place(
        "U2305", "USBLC6-2P6", "USBLC6-2P6 radio codec USB ESD", 520, 245,
        footprint=FOOTPRINTS["USBLC6-2P6"],
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        x = 20 + (idx // 5) * 210
        y = 330.2 + (idx % 5) * 12.7
        s.place(f"R{2310 + idx}", "R", f"{value} {label}", x, y, footprint=FOOTPRINTS["R"],
                pin_nets={"1": (net, "hier"), "2": (rail, "hier" if rail == "MCU_3V3" else "local")},
                extra_props={"Manufacturer": "Yageo", "MPN": "RC0603FR-0710KL" if value == "10k" else "RC0603FR-07100KL"})
    for idx, (net, label) in enumerate((
        ("RADIO_VHF_UART_RX", "VHF RX default low"),
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
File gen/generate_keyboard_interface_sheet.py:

from build_ducktop2 import Sheet, FOOTPRINTS


def mainboard_keyboard_connector_nets():
    """Map J310 through a same-side FFC to the manufactured J320 connector.

    J310 and J320 are both top-mounted, bottom-contact FH12 connectors. With the
    specified Type-A (contacts on the same side) FFC, physical pin n at J310
    reaches physical pin 31-n at J320.
    """
    nets = {
        "1": ("GND", "local"),
        "2": ("KB_FFC_5V", "local"),
        "3": ("KB_FFC_RGB_DATA", "local"),
        "27": ("KB_FFC_I2C_SDA", "local"),
        "28": ("KB_FFC_I2C_SCL", "local"),
        "29": ("KB_FFC_3V3", "local"),
        "30": ("GND", "local"),
        "MP": ("GND", "local"),
    }
    for pin, col in zip(range(4, 19), range(14, -1, -1)):
        nets[str(pin)] = (f"KB_FFC_COL{col}", "local")
    for pin, row in zip(range(19, 27), range(7, -1, -1)):
        nets[str(pin)] = (f"KB_FFC_ROW{row}", "local")
    return nets


def build(sheet_symbol_uuid):
    s = Sheet(f"/{sheet_symbol_uuid}")
    s.refcounters["#PWR"] = 310
    s.refcounters["#FLG"] = 310

    s.text(20, 12.7, "== Mainboard keyboard FFC interface ==")
    s.text(20, 20.32, "This sheet is the motherboard-side connector only; the MX ULP switches and diodes live on the separate keyboard PCB.")
    s.text(20, 27.94, "Keep this sheet in the main root so ducktop2.kicad_pcb imports only the laptop-side FFC connector, not keyboard-switch footprints.")

    s.place("J310", "Conn_01x30_FFC_MP", "Mainboard keyboard FFC to MX ULP daughterboard", 120, 150,
            footprint=FOOTPRINTS["Conn_01x30_FFC"], pin_nets=mainboard_keyboard_connector_nets(),
            extra_props={"Manufacturer": "Hirose", "MPN": "FH12-30S-0.5SH(55)"})

    for index in range(15):
        s.place(f"R{360 + index}", "R", "1k keyboard matrix series", 250, 45 + index * 10,
                footprint=FOOTPRINTS["R"],
                pin_nets={
                    "1": (f"KB_COL{index}", "hier"),
                    "2": (f"KB_FFC_COL{index}", "local"),
                })
    # R375 is deliberately removed from the matrix bank.  The manufactured
    # rev-A board leaves COL15 unused, so the same FFC conductor can carry a
    # future rev-B addressable-RGB data stream without changing rev A.
    s.place("R375", "R", "100R keyboard RGB data series", 250, 195,
            footprint=FOOTPRINTS["R"],
            pin_nets={
                "1": ("KB_RGB_DATA_5V", "local"),
                "2": ("KB_FFC_RGB_DATA", "local"),
            })

    for index in range(8):
        s.place(f"R{376 + index}", "R", "1k keyboard matrix series", 350, 45 + index * 10,
                footprint=FOOTPRINTS["R"],
                pin_nets={
                    "1": (f"KB_ROW{index}", "hier"),
                    "2": (f"KB_FFC_ROW{index}", "local"),
                })
    s.place("R384", "R", "100R keyboard I2C SCL series", 450, 45,
            footprint=FOOTPRINTS["R"],
            pin_nets={"1": ("I2C_SCL", "hier"), "2": ("KB_FFC_I2C_SCL", "local")})
    s.place("R385", "R", "100R keyboard I2C SDA series", 450, 60,
            footprint=FOOTPRINTS["R"],
            pin_nets={"1": ("I2C_SDA", "hier"), "2": ("KB_FFC_I2C_SDA", "local")})
    # Future keyboard RGB power is limited below the Molex 0150200315 cable's
    # 0.5 A/contact rating.  The switch and AHCT buffer both fail off while the
    # EC is resetting; rev A simply sees an unused, unpowered contact.
    s.place("U310", "TPS2553D", "TPS2553D keyboard RGB 5V switch 0.40A nominal",
            520, 55, footprint=FOOTPRINTS["TPS2553DDBV"],
            pin_nets={
                "1": ("SYS_5V", "hier"), "2": ("GND", "local"),
                "3": ("KB_RGB_PWR_EN", "hier"), "4": ("KB_RGB_FAULT_N", "hier"),
                "5": ("KB_RGB_ILIM", "local"), "6": ("KB_FFC_5V", "local"),
            },
            extra_props={
                "Manufacturer": "Texas Instruments", "MPN": "TPS2553DDBVR",
                "Datasheet": "https://www.ti.com/lit/ds/symlink/tps2553d.pdf",
            })
    s.place("R388", "R", "66.5k 1% keyboard RGB 0.40A ILIM", 590, 45,
            footprint=FOOTPRINTS["R"],
            pin_nets={"1": ("KB_RGB_ILIM", "local"), "2": ("GND", "local")})
    s.place("R389", "R", "100k keyboard RGB enable default-off", 590, 60,
            footprint=FOOTPRINTS["R"],
            pin_nets={"1": ("KB_RGB_PWR_EN", "hier"), "2": ("GND", "local")})
    s.place("R390", "R", "10k keyboard RGB fault pull-up", 590, 75,
            footprint=FOOTPRINTS["R"],
            pin_nets={"1": ("MCU_3V3", "hier"), "2": ("KB_RGB_FAULT_N", "hier")})
    s.place("C322", "C", "100n keyboard RGB switch input", 590, 90,
            footprint=FOOTPRINTS["C_100n"],
            pin_nets={"1": ("SYS_5V", "hier"), "2": ("GND", "local")})
    s.place("C323", "C", "100n keyboard RGB switch output", 590, 105,
            footprint=FOOTPRINTS["C_100n"],
            pin_nets={"1": ("KB_FFC_5V", "local"), "2": ("GND", "local")})

    s.place("U311", "74AHCT1G126", "SN74AHCT1G126 keyboard RGB 3V3-to-5V buffer",
            520, 130, footprint=FOOTPRINTS["SN74AHCT1G126DBV"],
            pin_nets={
                "1": ("KB_RGB_PWR_EN", "hier"), "2": ("KB_RGB_DATA_3V3", "hier"),
                "3": ("GND", "local"), "4": ("KB_RGB_DATA_5V", "local"),
                "5": ("SYS_5V", "hier"),
            },
            extra_props={
                "Manufacturer": "Texas Instruments", "MPN": "SN74AHCT1G126DBVR",
                "Datasheet": "https://www.ti.com/lit/ds/symlink/sn74ahct1g126.pdf",
            })
    s.place("R391", "R", "100k keyboard RGB data default-low", 590, 130,
            footprint=FOOTPRINTS["R"],
            pin_nets={"1": ("KB_RGB_DATA_3V3", "hier"), "2": ("GND", "local")})
    s.place("C324", "C", "100n keyboard RGB buffer local", 590, 145,
            footprint=FOOTPRINTS["C_100n"],
            pin_nets={"1": ("SYS_5V", "hier"), "2": ("GND", "local")})

    s.place("R386", "R", "0R DNP DO-NOT-FIT keyboard 5V protection bypass", 450, 90,
            footprint=FOOTPRINTS["R"], dnp=True,
            pin_nets={"1": ("SYS_5V", "hier"), "2": ("KB_FFC_5V", "local")})
    s.place("R387", "R", "0R keyboard RGB bus-buffer supply", 450, 105,
            footprint=FOOTPRINTS["R"],
            extra_props={"Manufacturer":"Yageo", "MPN":"RC0603JR-070RL"},
            pin_nets={"1": ("MCU_3V3", "hier"), "2": ("KB_FFC_3V3", "local")})

    s.place("C318", "C", "100n DNP keyboard 3V3 reserve", 450, 120,
            footprint=FOOTPRINTS["C_100n"], dnp=True,
            pin_nets={"1": ("KB_FFC_3V3", "local"), "2": ("GND", "local")})
    s.place("C319", "C", "10u keyboard RGB switched-output bulk", 300, 95,
            footprint=FOOTPRINTS["C_10u"],
            pin_nets={"1": ("KB_FFC_5V", "local"), "2": ("GND", "local")})

    # Anchor the sheet-local GND label to the project's global ground net.
    # Without this symbol, J310 pins 1/30/MP form an isolated hierarchical net.
    s.gnd(500, 135)

    s.text(20, 230, "NOTES:")
    s.text(20, 237.62, "J310 is deliberately pin-reversed relative to J320 for two top-side FH12 bottom-contact connectors and a Type-A same-side FFC.")
    s.text(20, 245.24, "Specified cable: Molex 0150200315, 30 circuits, 0.5 mm pitch, 30 mm, Type A / same-side contacts.")
    s.text(20, 252.86, "R386 stays DNP. Fit R387 for the RGB keyboard bus buffer. U310 limits the switched 5 V rail and defaults off.")
    s.text(20, 260.48, "J310 pin 3 / J320 pin 28 is an unused one-wire data option. The RGB keyboard uses I2C on J320 pins 3/4.")
    s.text(20, 268.1, "RGB keyboard U320 uses a 33.2k current-setting resistor. Budget 0.25A on the switched 5V feed and verify full-white current on hardware.")

    return s
